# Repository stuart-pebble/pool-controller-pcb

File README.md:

# Pool Controller PCB

KiCad design for a Connect 10 compatible pool-bus interface, using the finished **Waveshare ESP32-C6 Mini Development Board (ESP32-C6-Zero)** plugged into a carrier socket. The board provides a 5 V buck supply and single-wire receive/transmit interface. Firmware is maintained in [pool-controller-code](https://github.com/marklynch/pool-controller-code).

## Current revision

**Revision 15 is a prototype for validation.** It adds the 3.3 V RX clamp from [issue #3](https://github.com/marklynch/pool-controller-pcb/issues/3) and changes the TX base resistor to 560 Ω as proposed in [issue #4](https://github.com/marklynch/pool-controller-pcb/issues/4). It retains the existing 80 × 75 mm outline and 1.2 mm thickness.

The RX clamp requires the Waveshare 3.3 V rail and does not provide power-off isolation. Confirm operation during boot/reset/shutdown and at both 7 V and 12 V data-high levels before field use. The power-supply design report's detailed operating point is **5 V / 0.5 A**; a 5 A regulator IC does not make this a 5 A board.

See [revision 15 assembly and acceptance](docs/rev15-assembly.md) before ordering. J1/J2 now specify distributor-stocked Ckmtw R-RJ11R06P-A000 (LCSC C2902699), with a matching new footprint and connector routing. Confirm the larger connector’s enclosure clearance and snap-peg retention on the 1.2 mm board with PCBWay. The Waveshare boards have already been purchased separately; PCBWay should supply the soldered carrier and its socket, with no additional module purchase.

## Files

- `PoolController.kicad_pro`, `.kicad_sch`, `.kicad_pcb`: source project, schematic and routed PCB.
- `components/`: project-specific symbols, footprints and existing 3D models.
- `docs/`: component/design references and prototype assembly instructions.
- `manufacturing/rev15/`: revision-specific sample-order exports and validation record.
- `scripts/export-manufacturing.sh`: reproduce manufacturing exports using KiCad 9.

Use **KiCad 9** to open and validate the project. Custom library paths are relative to the project. A 3D model is not a substitute for checking the dimensions and pin mapping of the actual purchased part.

## Ordering prototypes

For PCBWay, use `PCBWay-BOM.csv` (carrier parts only; Waveshare boards are customer-supplied) and `PCBWay-SMT-CPL.csv`. Read the assembly notes, confirm legacy-part stock and module installation, and review their DFM and placement previews before authorizing fabrication/assembly. Gerbers and drill files cover the bare board; the BOM, placement file and assembly drawing define fitted carrier parts. Fit the customer-owned module after delivery, or arrange consignment and separately quote installation/programming with PCBWay.

Physical checks, supplier approval, firmware programming and functional testing are distinct from KiCad ERC/DRC. Generated files are a prototype build package, not proof of field reliability.

## Licence

Hardware designs are licensed under the CERN Open Hardware Licence Version 2 — Permissive; see [LICENCE](LICENCE). See [CHANGELOG.md](CHANGELOG.md) for revision history.

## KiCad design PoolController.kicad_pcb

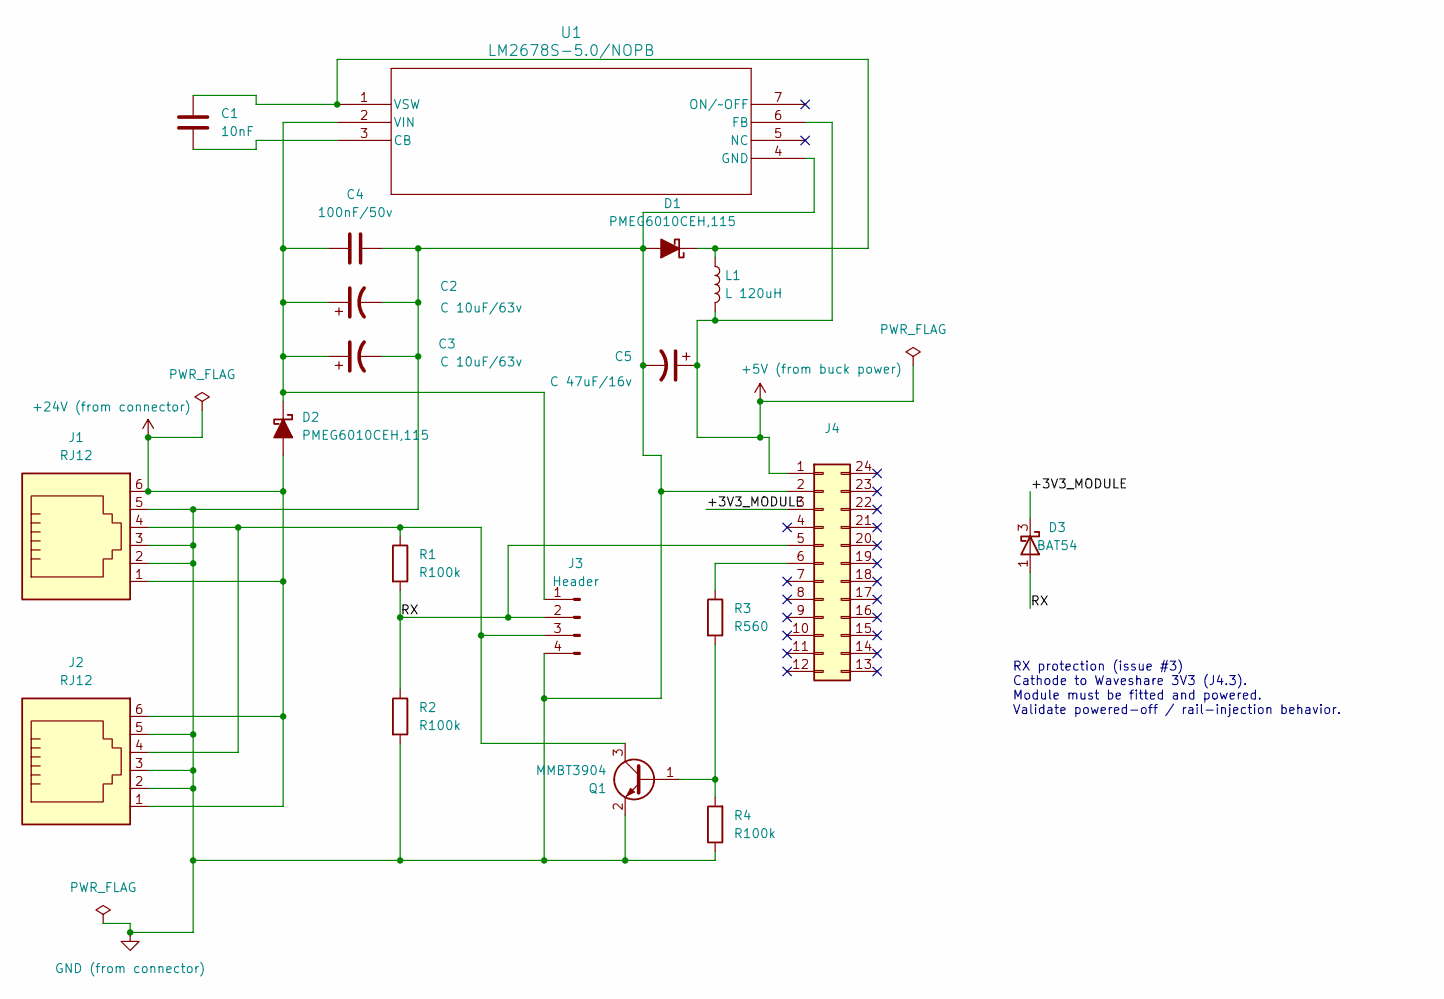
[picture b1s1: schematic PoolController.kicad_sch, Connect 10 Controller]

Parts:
C1: 10nF; C_0805_2012Metric; MPN C2012C0G1H103K060AA
C2, C3: C 10uF/63v; C_1210_3225Metric; MPN GRM32ER71J106KA12L
C4: 100nF/50v; C_0805_2012Metric; MPN C0805C104M5RACTU
C5: C 47uF/16v; C_1210_3225Metric; MPN GRM32ER61C476KE15L
D1, D2: PMEG6010CEH,115; D_SOD-123F; MPN PMEG6010CEH,115
D3: BAT54; SOT-23; MPN BAT54,215
J1, J2: RJ12; RJ12_Ckmtw_R-RJ11R06P-A000; MPN R-RJ11R06P-A000
J3: Header; PinHeader_1x04_P2.54mm_Vertical; MPN PZ254V-11-04P
J4: Conn_02x12_Counter_Clockwise; DIP-24_18.0mmx34.29mm_W15.24mm_Socket; MPN DILB24P-223TLF
L1: L 120uH; L_10.4x10.4_H4.8; MPN SRR1050A-121Y
Q1: MMBT3904; SOT-23_MCC; MPN MMBT3904
R1, R2, R4: R100k; R_0603_1608Metric; MPN RC0603FR-07100KL
R3: R560; R_0603_1608Metric; MPN RC0603FR-07560RL
U1: LM2678S-5.0/NOPB; TO-263-7_TabPin4; MPN LM2678S-5.0/NOPB

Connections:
+5V (from buck power): C5.1, J4.1, L1.2, U1.6 (FB)
+24V (from connector): D2.2 (A), J1.1, J1.6, J2.1, J2.6
/+3V3_MODULE: D3.3 (K), J4.3
/RX: D3.1 (A), J3.2, J4.5, R1.2, R2.1
GND (from connector): C2.2, C3.2, C4.2, C5.2, D1.2 (A), J1.2, J1.3, J1.5, J2.2, J2.3, J2.5, J3.4, J4.2, Q1.2 (E), R2.2, R4.1, U1.4 (GND)
unnamed: C1.1, D1.1 (K), L1.1, U1.1 (VSW)
unnamed: C2.1, C3.1, C4.1, D2.1 (K), J3.1, U1.2 (VIN)
unnamed: J1.4, J2.4, J3.3, Q1.3 (C), R1.1
unnamed: J4.6, R3.1
unnamed: Q1.1 (B), R3.2, R4.2
unnamed: C1.2, U1.3 (CB)

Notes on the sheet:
RX protection (issue #3) Cathode to Waveshare 3V3 (J4.3). Module must be fitted and powered. Validate powered-off / rail-injection behavior.

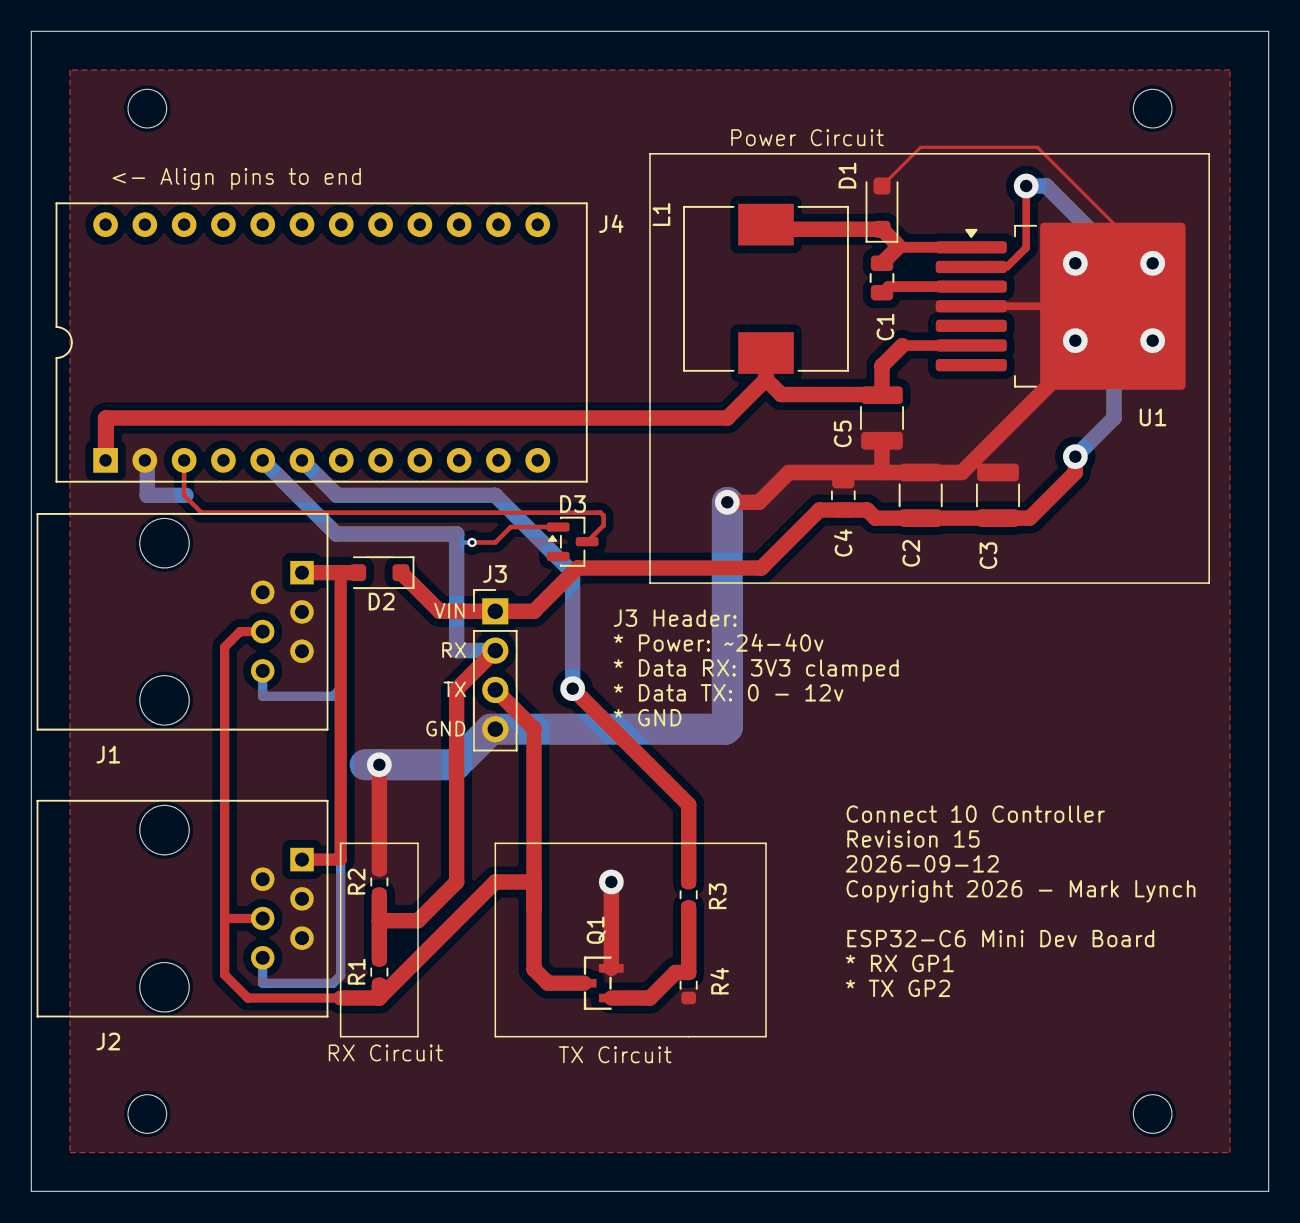
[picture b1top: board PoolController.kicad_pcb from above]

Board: 2 copper layers, 80.0 x 75.0 mm, 19 parts (0 on the bottom side), 11 nets.

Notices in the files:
PoolController.kicad_pcb:
Copyright 2026 - Mark Lynch
